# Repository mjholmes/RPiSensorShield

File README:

A Remote sensor shield that fits over a second generation Raspberry Pi and allows a XBee S2 Zigbee transciever, a BMP085 pressure sensor, a DS1820 1-Wire temperature sensor nad a ThingM BlinkM to be connected.

The XBee connects to the Pi's ttyAMA0 serial interface, the DS1820 uses 1-wire on a GPIO port, the other devices use i2c (3.3v and 5v with translation) on i2c port 1.

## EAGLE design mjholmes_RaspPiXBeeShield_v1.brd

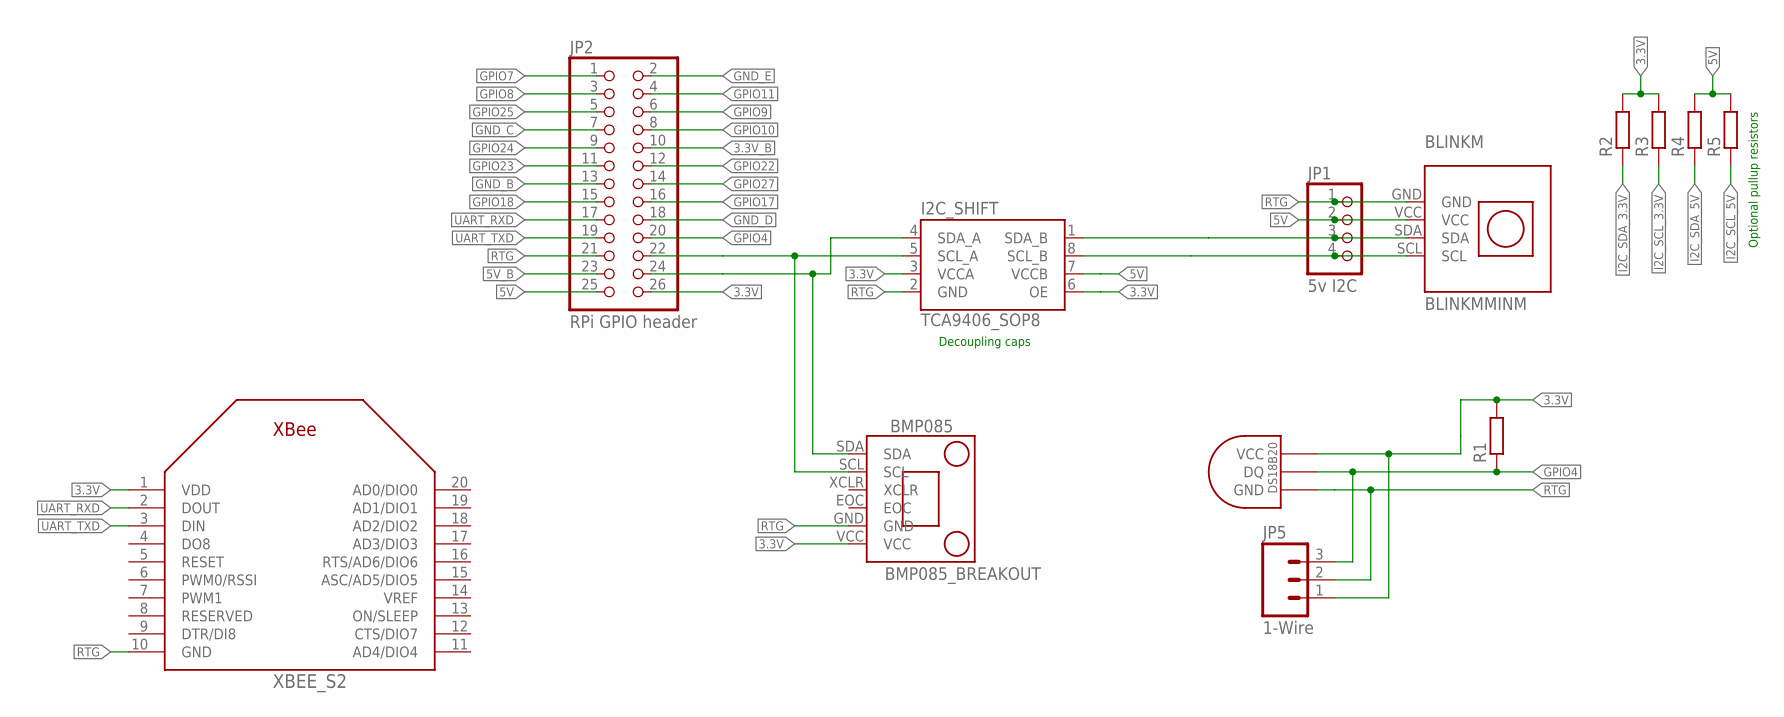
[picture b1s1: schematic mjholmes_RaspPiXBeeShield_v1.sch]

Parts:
BLINKM: BLINKMMINM; BLINKM_MINM
BMP085: BMP085_BREAKOUT
I2C_SHIFT: TCA9406_SOP8; SOP8
JP1: 5v I2C; 1X04
JP2: RPi GPIO header; 2X13
JP5: 1-Wire; JST-3-PTH
R1, R2, R3, R4, R5: R-EU_R0603; R0603
U$3: DS1820SOIC; DS18B20_SOIC
XBEE_S2: XBEE S2; XBEE_S2

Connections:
3.3V: BMP085.VCC, I2C_SHIFT.3 (VCCA), I2C_SHIFT.6 (OE), JP2.26, JP5.1, R1.2, R2.2, R3.2, U$3.VCC, XBEE_S2.1 (VDD)
3.3V_B: JP2.10
5V: BLINKM.VCC, I2C_SHIFT.7 (VCCB), JP1.2, JP2.25, R4.2, R5.2
5V_B: JP2.23
GND_B: JP2.13
GND_C: JP2.7
GND_D: JP2.18
GND_E: JP2.2
GPIO4: JP2.20, JP5.3, R1.1, U$3.DQ
GPIO7: JP2.1
GPIO8: JP2.3
GPIO9: JP2.6
GPIO10: JP2.8
GPIO11: JP2.4
GPIO17: JP2.16
GPIO18: JP2.15
GPIO22: JP2.12
GPIO23: JP2.11
GPIO24: JP2.9
GPIO25: JP2.5
GPIO27: JP2.14
I2C_SCL_3.3V: BMP085.SCL, I2C_SHIFT.5 (SCL_A), JP2.22, R3.1
I2C_SCL_5V: BLINKM.SCL, I2C_SHIFT.8 (SCL_B), JP1.4, R5.1
I2C_SDA_3.3V: BMP085.SDA, I2C_SHIFT.4 (SDA_A), JP2.24, R2.1
I2C_SDA_5V: BLINKM.SDA, I2C_SHIFT.1 (SDA_B), JP1.3, R4.1
RTG: BLINKM.GND, BMP085.GND, I2C_SHIFT.2 (GND), JP1.1, JP2.21, JP5.2, U$3.GND, XBEE_S2.10 (GND)
UART_RXD: JP2.17, XBEE_S2.2 (DOUT)
UART_TXD: JP2.19, XBEE_S2.3 (DIN)

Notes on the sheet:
Decoupling caps
Optional pullup resistors

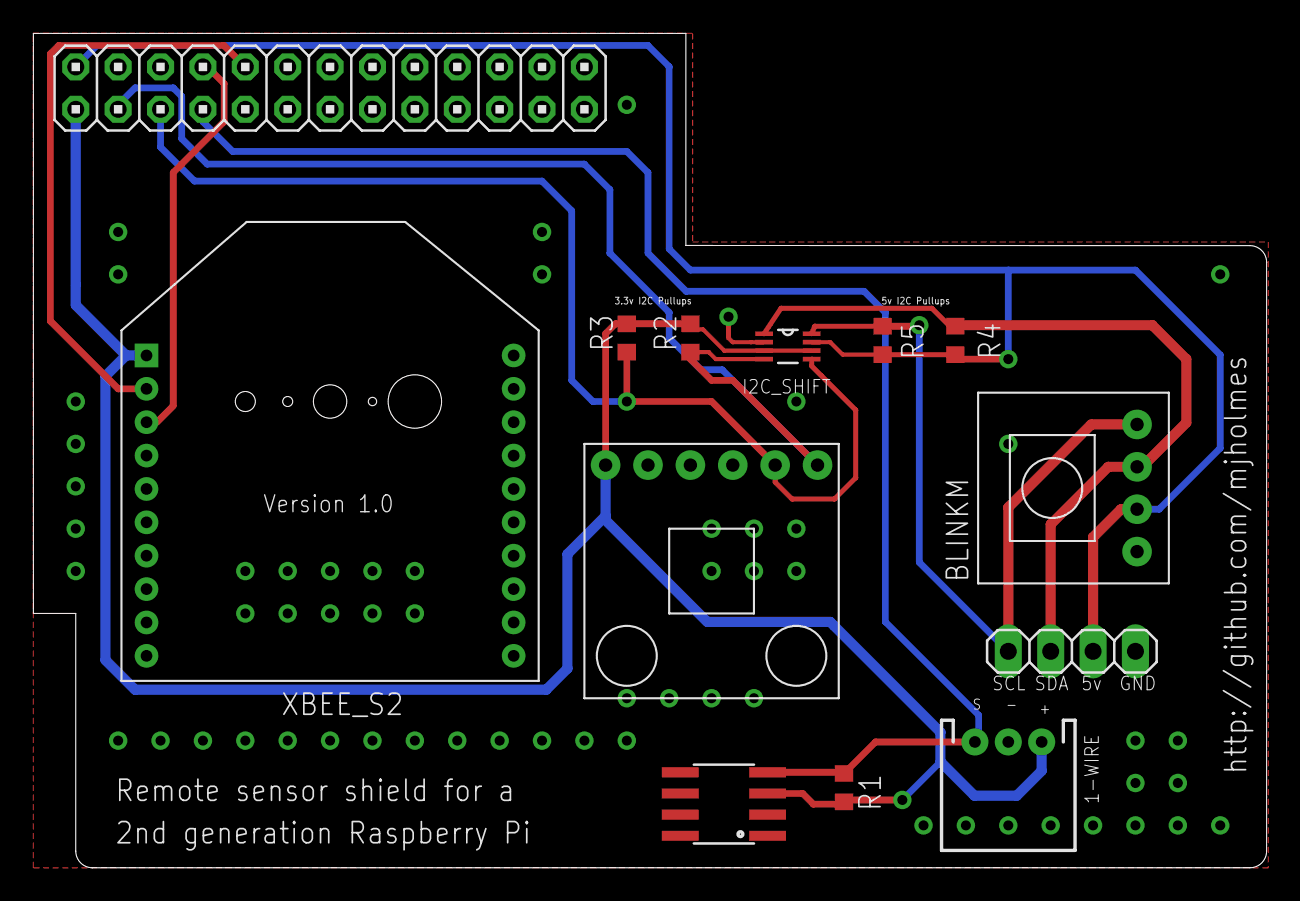
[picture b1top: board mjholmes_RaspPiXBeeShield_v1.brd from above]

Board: 2 copper layers, 73.9 x 50.0 mm, 13 parts (0 on the bottom side), 10 nets.

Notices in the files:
parts and their libraries:
SparkFun: Licensing: CC v3.0 Share-Alike You are welcome to use this library for commercial purposes.
